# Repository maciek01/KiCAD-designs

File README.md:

# KiCAD-designs

LORA peer-to-peer: https://github.com/maciek01/KiCAD-designs/tree/main/arduino-nano-esp32
code: https://github.com/maciek01/lora-esp32-s3-rfm95w

LORAWAN TTN and CHIRPSTACK: https://github.com/maciek01/KiCAD-designs/tree/main/esp32-s3-wroom-2-devkitc1
code: https://github.com/maciek01/lorawan-esp32-s3-rfm95w

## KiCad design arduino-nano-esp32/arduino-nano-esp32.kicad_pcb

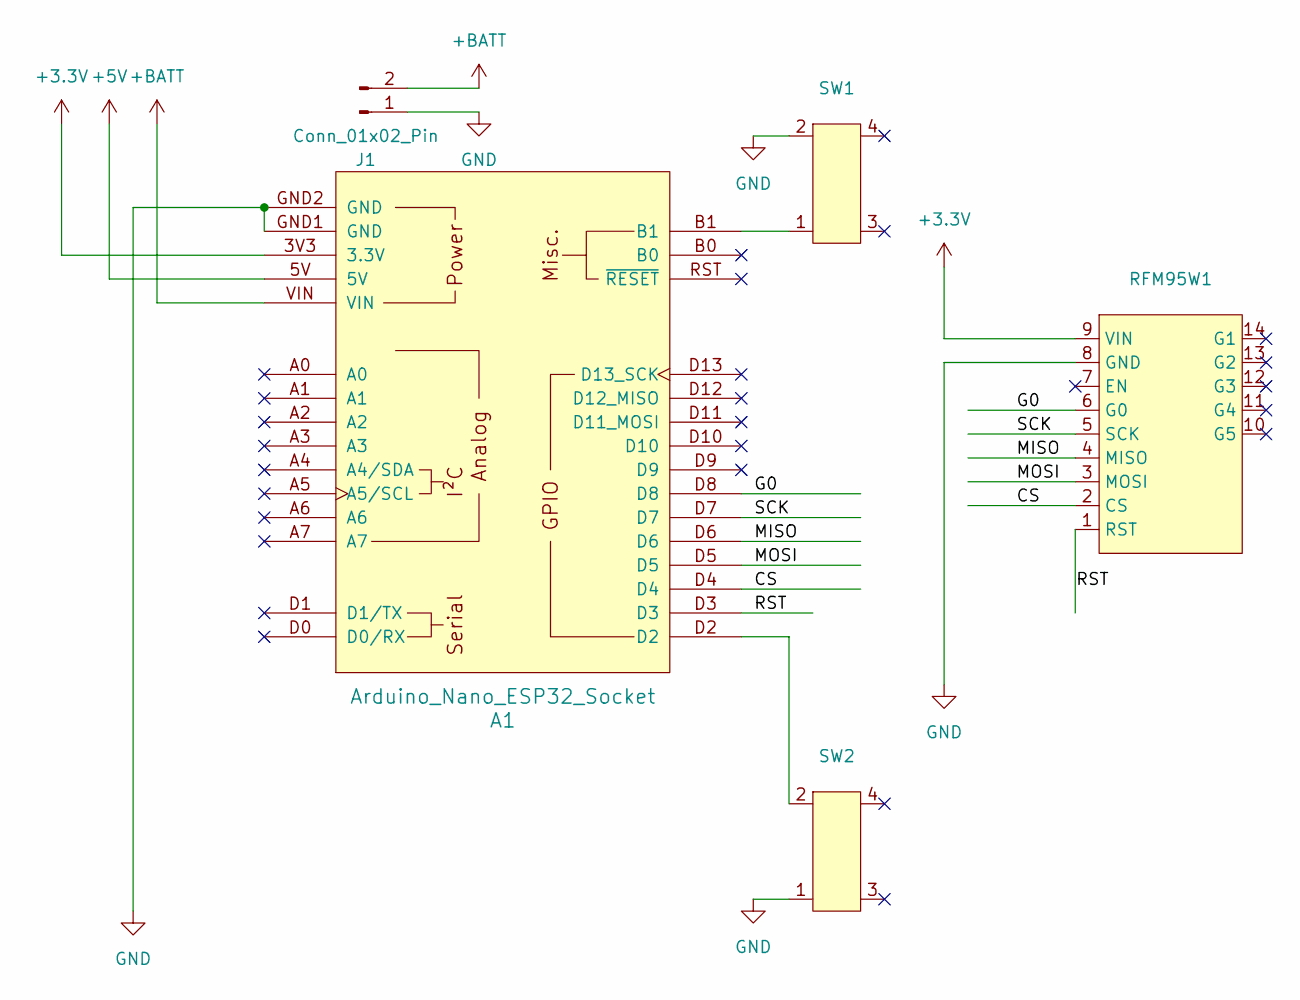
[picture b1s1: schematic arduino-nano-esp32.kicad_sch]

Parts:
A1: Arduino_Nano_ESP32_Socket
J1: Conn_01x02_Pin; PinHeader_1x02_P2.54mm_Horizontal
RFM95W1: lora-adafruit
SW1, SW2: 3x4 switch

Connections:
+3.3V: A1.3V3 (3.3V), RFM95W1.9 (VIN)
+5V: A1.5V
+BATT: A1.VIN, J1.2
/CS: A1.D4, RFM95W1.2 (CS)
/G0: A1.D8, RFM95W1.6 (G0)
/MISO: A1.D6, RFM95W1.4 (MISO)
/MOSI: A1.D5, RFM95W1.3 (MOSI)
/RST: A1.D3, RFM95W1.1 (RST)
/SCK: A1.D7, RFM95W1.5 (SCK)
GND: A1.GND1 (GND), A1.GND2 (GND), J1.1, RFM95W1.8 (GND), SW1.2, SW2.1
unnamed: A1.B1, SW1.1
unnamed: A1.D2, SW2.2

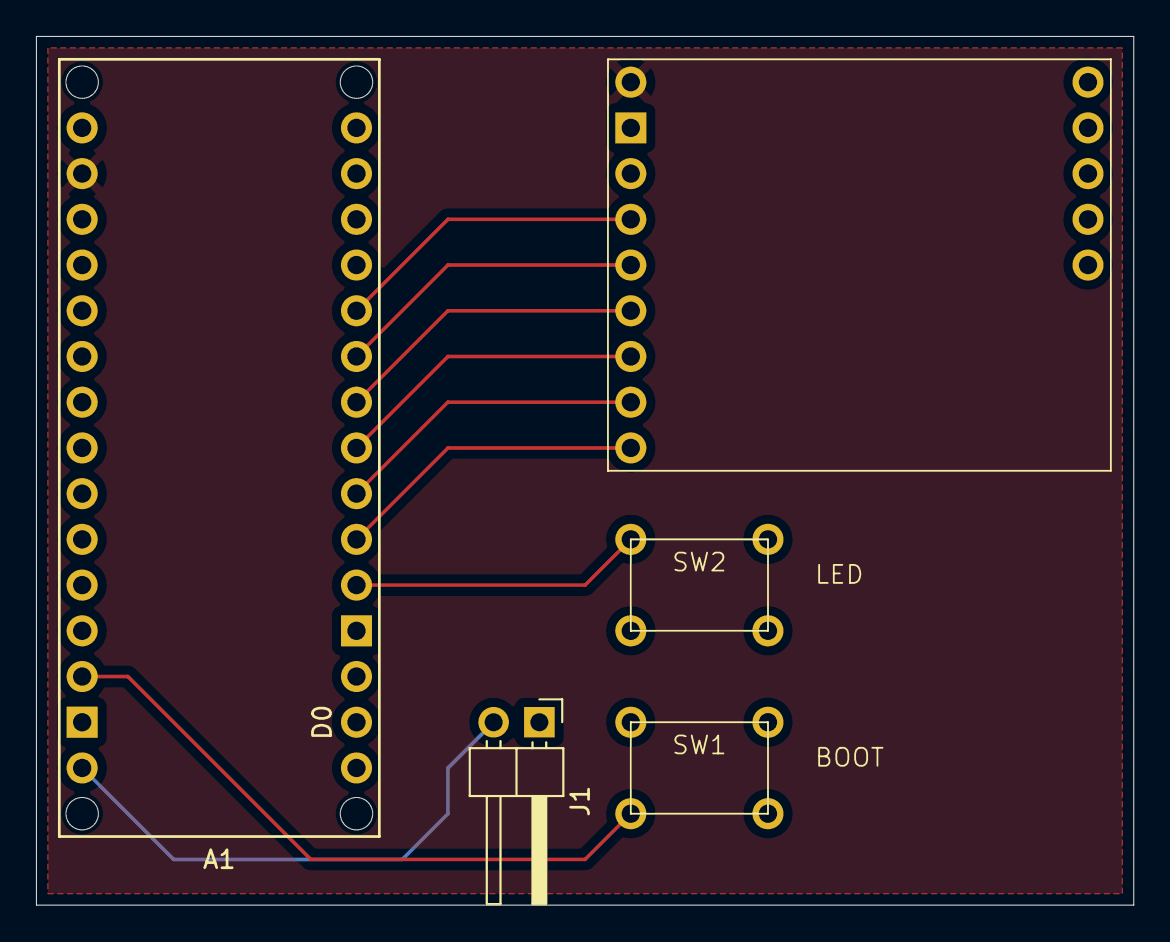
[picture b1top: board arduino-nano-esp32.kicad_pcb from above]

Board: 2 copper layers, 61.0 x 48.3 mm, 5 parts (0 on the bottom side), 11 nets.

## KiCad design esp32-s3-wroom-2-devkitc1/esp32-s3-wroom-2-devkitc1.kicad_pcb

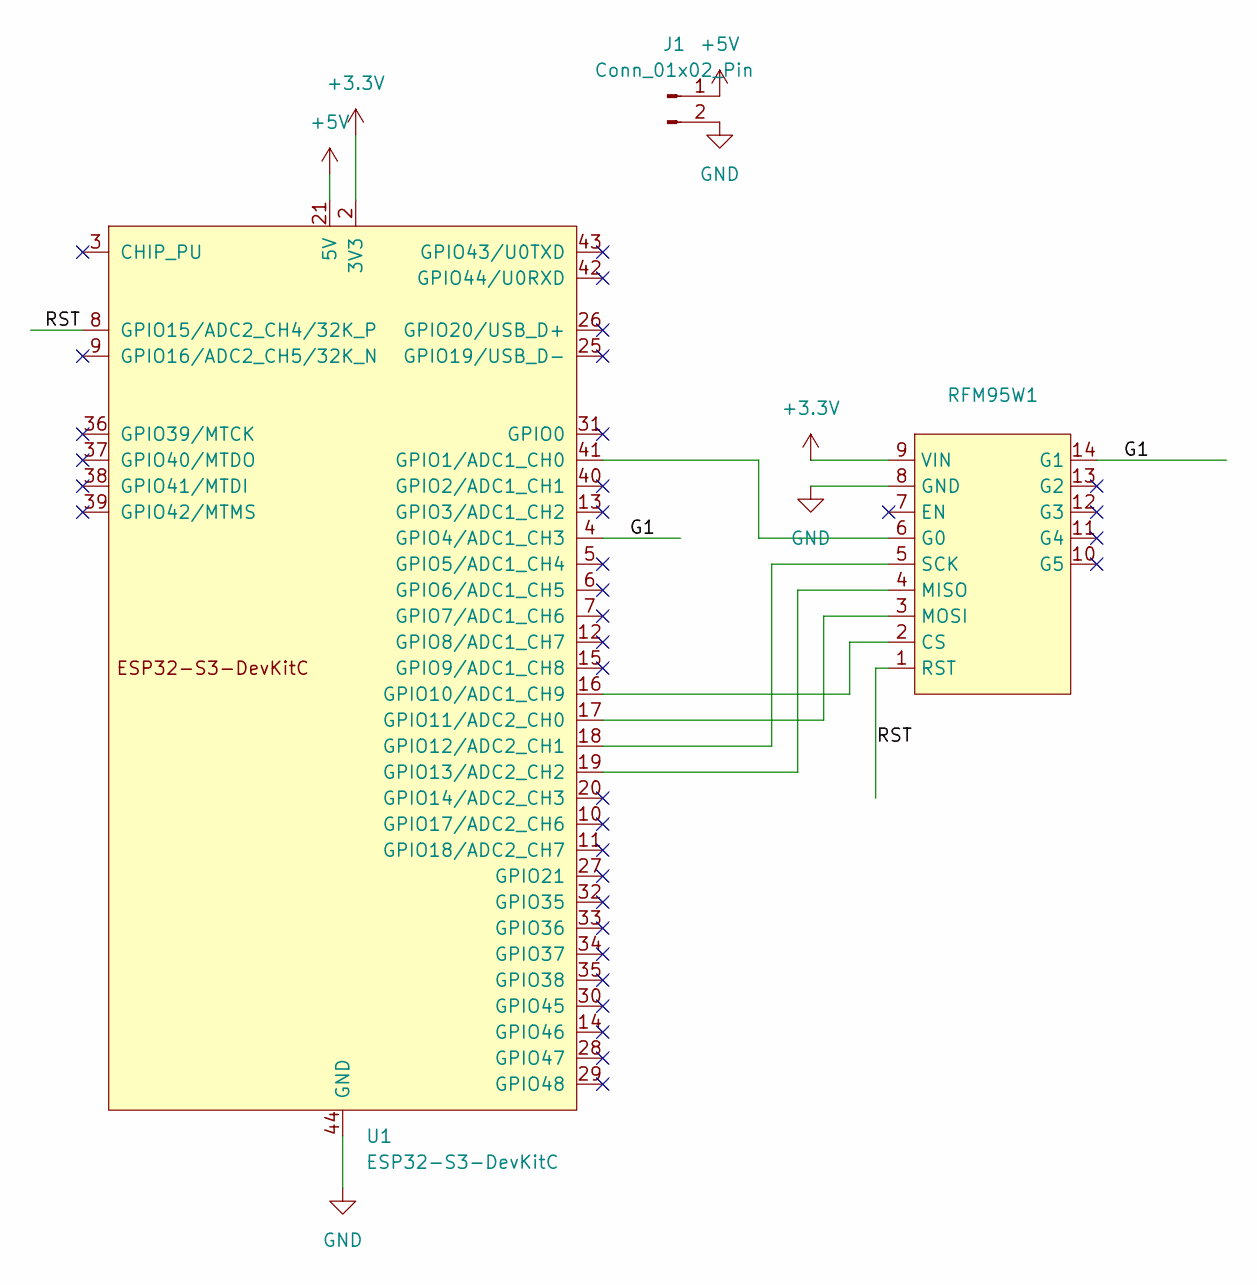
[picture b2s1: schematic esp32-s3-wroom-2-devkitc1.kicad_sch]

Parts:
J1: Conn_01x02_Pin; PinHeader_1x02_P2.54mm_Horizontal
RFM95W1: lora-adafruit
U1: ESP32-S3-DevKitC

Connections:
+3.3V: RFM95W1.9 (VIN), U1.1 (3V3), U1.2 (3V3)
+5V: J1.1, U1.21 (5V)
/G1: RFM95W1.14 (G1), U1.4 (GPIO4/ADC1_CH3)
/RST: RFM95W1.1 (RST), U1.8 (GPIO15/ADC2_CH4/32K_P)
GND: J1.2, RFM95W1.8 (GND), U1.22 (GND), U1.23 (GND), U1.24 (GND), U1.44 (GND)
unnamed: RFM95W1.2 (CS), U1.16 (GPIO10/ADC1_CH9)
unnamed: RFM95W1.6 (G0), U1.41 (GPIO1/ADC1_CH0)
unnamed: RFM95W1.4 (MISO), U1.19 (GPIO13/ADC2_CH2)
unnamed: RFM95W1.3 (MOSI), U1.17 (GPIO11/ADC2_CH0)
unnamed: RFM95W1.5 (SCK), U1.18 (GPIO12/ADC2_CH1)

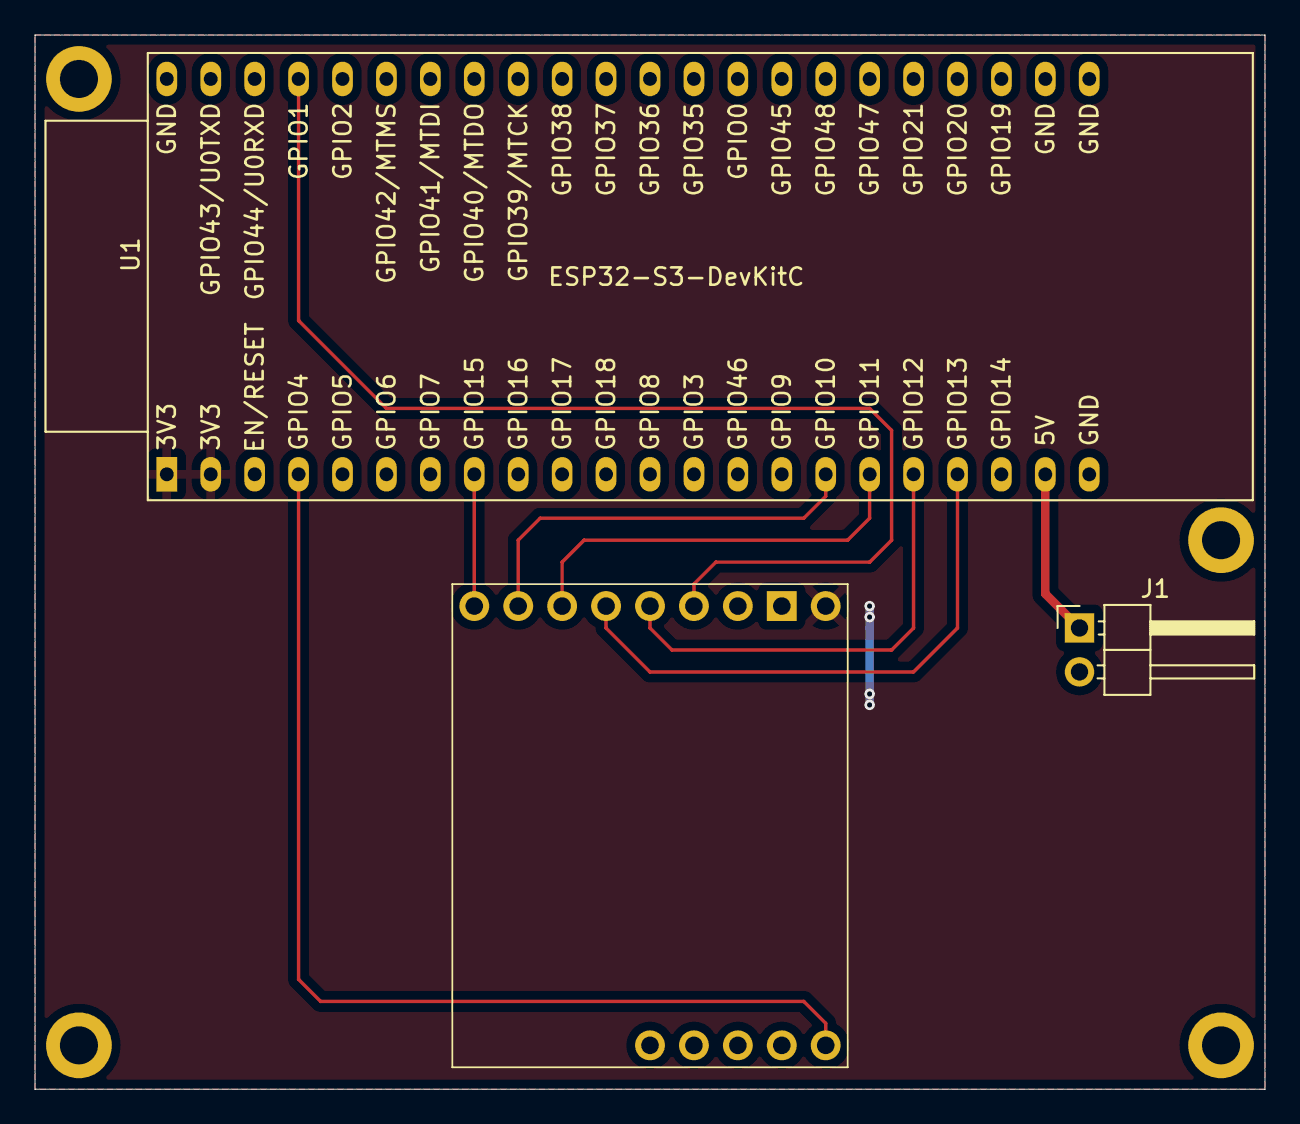
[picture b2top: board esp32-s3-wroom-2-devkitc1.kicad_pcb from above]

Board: 2 copper layers, 71.1 x 61.0 mm, 3 parts (0 on the bottom side), 10 nets.

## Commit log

2024-06-19 initial add
2024-06-19 cleanup
2024-06-19 footprint lib
2024-06-19 symbol lib
2024-06-19 gen gerbers
2024-06-19 net class plus cleanup
2024-06-22 add nests and 3v3 area
2024-07-02 need bigger holes
